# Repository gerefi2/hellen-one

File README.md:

# TL,DR: 

hellen-one is a toolset to produce custom PCBs by merging gerber files of known proven functional modules into trivial _frame_ PCB with mostly just the main vehicle connector.

* fork https://github.com/gerefi/hellen-example/ repo to get github actions and meta files
* make sure github actions are enabled/enable github actions on your fork
* replace xxx and yyy in ``revision.txt`` with name of your board
* create youboard.kicad_pcb from [proven modules](https://github.com/gerefi2/hellen-one/tree/master/modules) using KiCAD 6 or 7
* push into github to trigger hellen-one gerber expert and gerber merge (that's where the hellen magic happens! for instance gerber export is taken care by [export.sh](https://github.com/gerefi2/hellen-one/blob/master/kicad/bin/export.sh) script which github action would invoke _automatically_. Just watch for the yellow circle to turn into a green checkmark.)
* (sorry rotation only by factor of 90 degrees at this point)
* order your using fabrication files from 'boards' folder!

Please see how some of the open source boards are done and follow the pattern:

## Open Source Boards

* https://github.com/gerefi/alphax-4chan
* https://github.com/gerefi/uaefi
* https://github.com/gerefi/alphax-2chan
* https://github.com/gerefi/hellen154hyundai
* https://github.com/gerefi/hellen121vag
* https://github.com/gerefi/hellen88bmw
* https://github.com/gerefi2/hellen81/

This repository contains all scripts and data to create Hellen One boards for [gerefi](https://github.com/gerefi/gerefi)!

See also https://github.com/gerefi/gerefi/wiki/Hellen-One-Platform

Hellen One is a DIY PnP ECU board construction toolset.

Do you have a car with a rare or non-standard ECU connector pinout?
Do you want a custom DIY ECU but don't want to design it from scratch?

Then Hellen One is for you!

Please see Hellen One Wiki for more info:

https://github.com/gerefi2/hellen-one/wiki

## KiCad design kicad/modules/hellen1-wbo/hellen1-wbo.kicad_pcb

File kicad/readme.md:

# Some of the modules were designed in KiCAD

If you are designing a new ECU frame see https://github.com/gerefi2/hellen-one/tree/master/modules

doThis folder contains module _source_ files, not reusable resulting frames like [here](../modules).

See https://github.com/gerefi2/hellen-one/wiki/scripts-howto#how-to-create-a-module

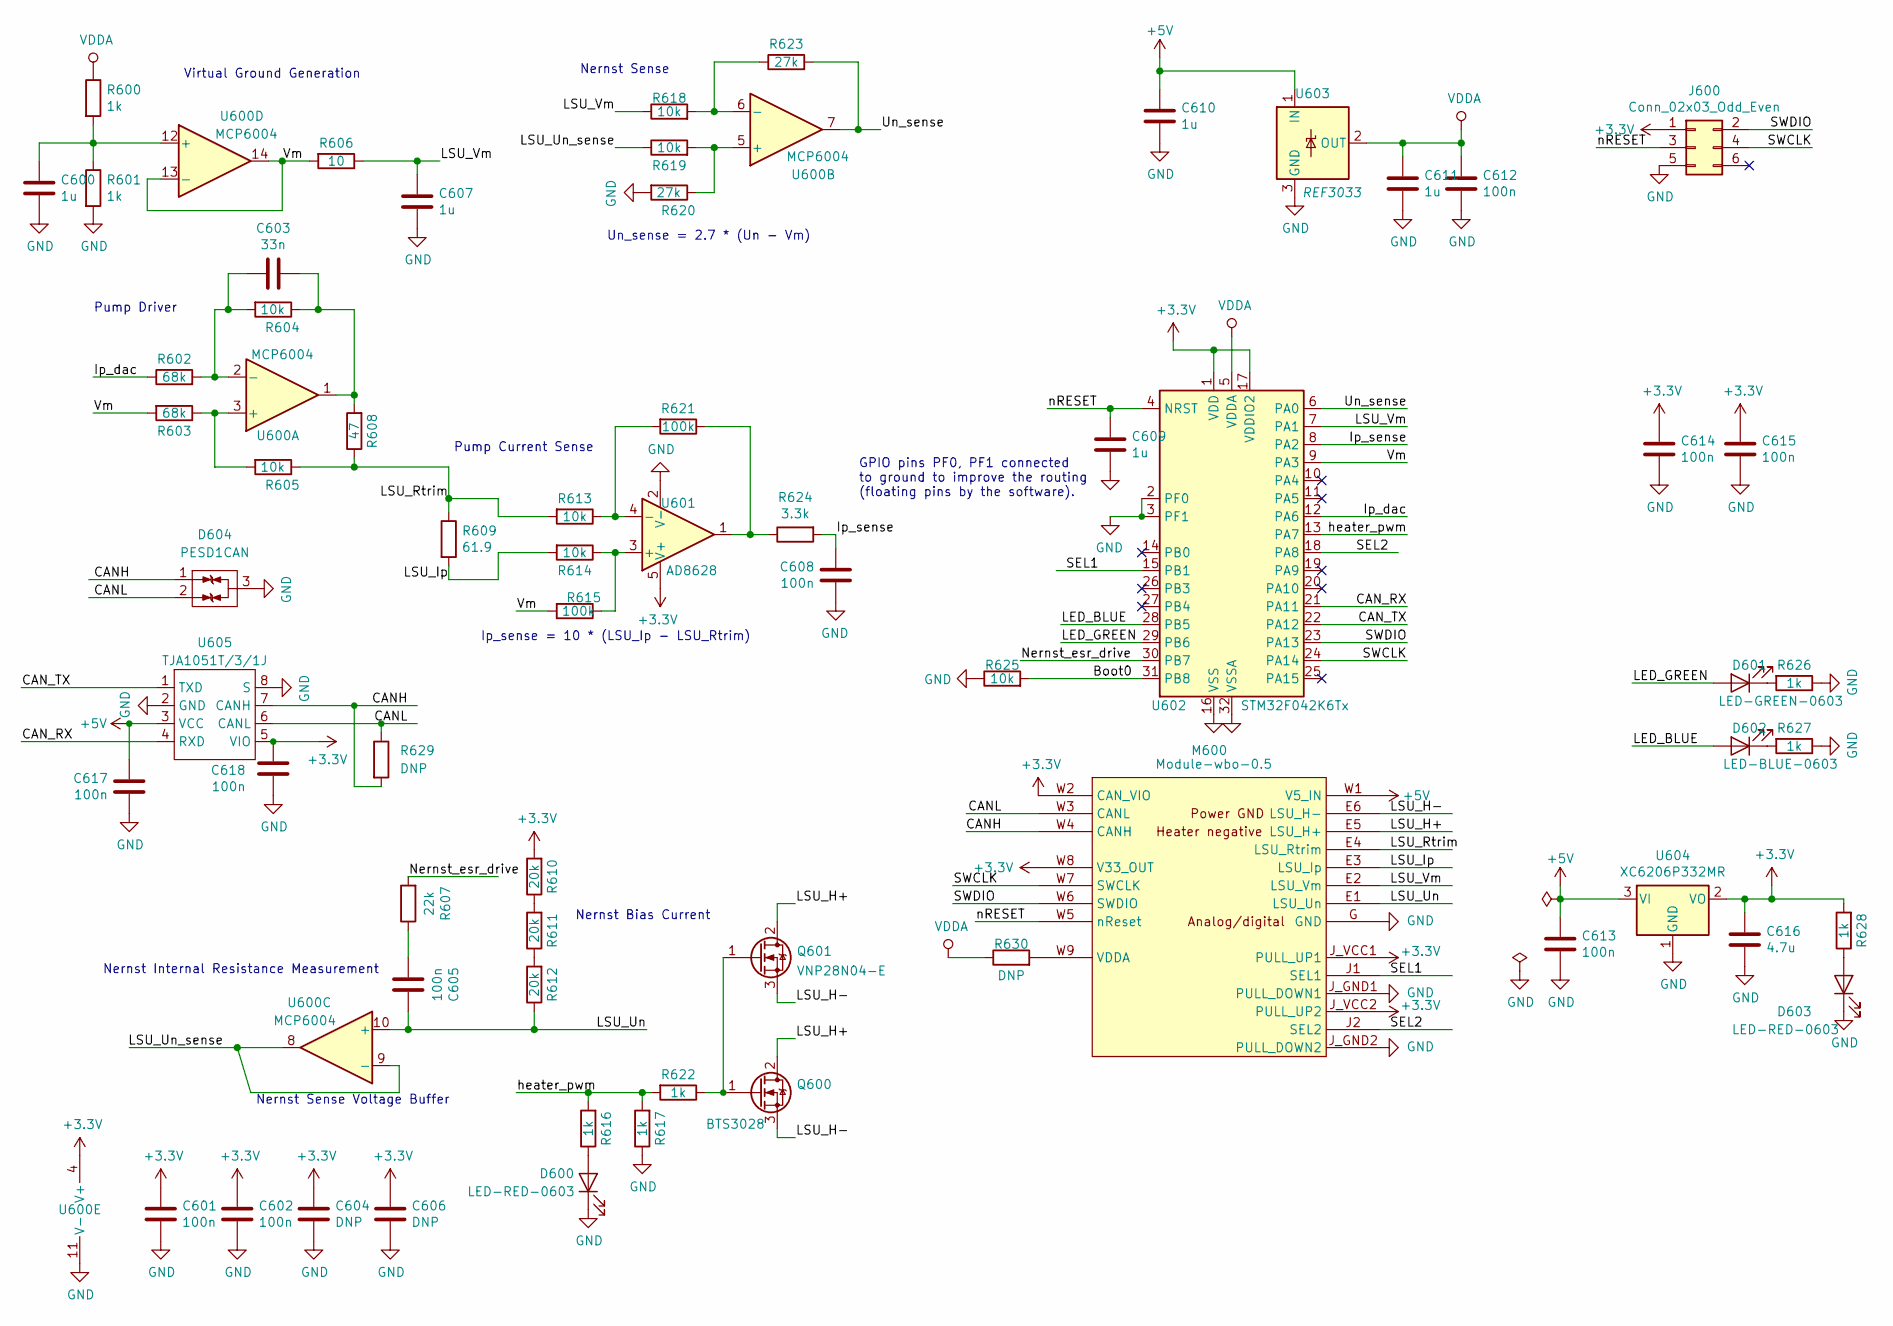
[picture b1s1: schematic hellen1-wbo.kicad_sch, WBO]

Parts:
C600, C607, C609, C610, C611: 1u; C_0402_1005Metric; LCSC C52923
C601, C602, C605, C608, C612, C613, C614, C615, C617, C618: 100n; C_0402_1005Metric; LCSC C1525
C603: 33n; C_0402_1005Metric; LCSC C1585
C604, C606: DNP; C_0402_1005Metric
C616: 4.7u; C_0603_1608Metric; LCSC C19666
D600, D603: LED-RED-0603; LED_0603_1608Metric; LCSC C2286
D601: LED-GREEN-0603; LED_0603_1608Metric; LCSC C72043
D602: LED-BLUE-0603; LED_0603_1608Metric; LCSC C72041
D604: PESD1CAN; SOT-23; LCSC C343993
J600: Conn_02x03_Odd_Even; Tag-Connect_TC2030-IDC-NL_2x03_P1.27mm_Vertical
M600: Module-wbo-0.5; wbo
Q600: BTS3028; TO-252-2; LCSC C112639
Q601: VNP28N04-E; TO-220-3_Vertical; LCSC C263002
R600, R601, R616, R617, R622, R626, R627, R628: 1k; R_0402_1005Metric; LCSC C11702
R602, R603: 68k; R_0402_1005Metric; LCSC C36871
R604, R605, R613, R614, R618, R619, R625: 10k; R_0402_1005Metric; LCSC C25744
R606: 10; R_0402_1005Metric; LCSC C25077
R607: 22k; R_0402_1005Metric; LCSC C25768
R608: 47; R_0402_1005Metric; LCSC C25118
R609: 61.9; R_0603_1608Metric; LCSC C23092
R610, R611, R612: 20k; R_0402_1005Metric; LCSC C25765
R615, R621: 100k; R_0402_1005Metric; LCSC C25741
R620, R623: 27k; R_0402_1005Metric; LCSC C25771
R624: 3.3k; R_0402_1005Metric; LCSC C25890
R629, R630: DNP; R_0402_1005Metric
U600: MCP6004; TSSOP-14_4.4x5mm_P0.65mm; LCSC C50282
U601: AD8628; TSOT-23-5; LCSC C29309
U602: STM32F042K6Tx; LQFP-32_7x7mm_P0.8mm; LCSC C69216
U603: REF3033; SOT-23; LCSC C36658
U604: XC6206P332MR; SOT-23; LCSC C5446
U605: TJA1051T/3/1J; SO-8_3.9x4.9mm_P1.27mm; LCSC C38695

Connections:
+3V3: C601.1, C602.1, C604.1, C606.1, C614.1, C615.1, C616.1, C618.1, J600.1, M600.J_VCC1 (PULL_UP1), M600.J_VCC2 (PULL_UP2), M600.W2 (CAN_VIO), M600.W8 (V33_OUT), R610.2, R628.2, U600.4 (V+), U601.5 (V+), U602.1 (VDD), U602.17 (VDDIO2), U604.2 (VO), U605.5 (VIO)
+5V: C610.1, C613.1, C617.1, M600.W1 (V5_IN), U603.1 (IN), U604.3 (VI), U605.3 (VCC)
/Boot0: R625.2, U602.31 (PB8)
/CANH: D604.1 (G), M600.W4 (CANH), R629.2, U605.7 (CANH)
/CANL: D604.2 (D), M600.W3 (CANL), R629.1, U605.6 (CANL)
/CAN_RX: U602.21 (PA11), U605.4 (RXD)
/CAN_TX: U602.22 (PA12), U605.1 (TXD)
/Ip_dac: R602.1, U602.12 (PA6)
/Ip_sense: C608.1, R624.2, U602.8 (PA2)
/LED_BLUE: D602.2 (A), U602.28 (PB5)
/LED_GREEN: D601.2 (A), U602.29 (PB6)
/LSU_H+: M600.E5 (LSU_H+), Q600.2 (D), Q601.2 (D)
/LSU_H-: M600.E6 (LSU_H-), Q600.3 (S), Q601.3 (S)
/LSU_Ip: M600.E3 (LSU_Ip), R609.2, R614.2
/LSU_Rtrim: M600.E4 (LSU_Rtrim), R605.1, R608.1, R609.1, R613.2
/LSU_Un: C605.1, M600.E1 (LSU_Un), R612.1, U600.10 (+)
/LSU_Un_sense: R619.1, U600.8, U600.9 (-)
/LSU_Vm: C607.1, M600.E2 (LSU_Vm), R606.1, R618.1, U602.7 (PA1)
/Nernst_esr_drive: R607.2, U602.30 (PB7)
/SEL1: M600.J1 (SEL1), U602.15 (PB1)
/SEL2: M600.J2 (SEL2), U602.18 (PA8)
/SWCLK: J600.4, M600.W7 (SWCLK), U602.24 (PA14)
/SWDIO: J600.2, M600.W6 (SWDIO), U602.23 (PA13)
/Un_sense: R623.2, U600.7, U602.6 (PA0)
/Vm: R603.2, R606.2, R615.2, U600.13 (-), U600.14, U602.9 (PA3)
/heater_pwm: R616.2, R617.2, R622.2, U602.13 (PA7)
/nRESET: C609.1, J600.3, M600.W5 (nReset), U602.4 (NRST)
GND: C600.2, C601.2, C602.2, C604.2, C606.2, C607.2, C608.2, C609.2, C610.2, C611.2, C612.2, C613.2, C614.2, C615.2, C616.2, C617.2, C618.2, D600.1 (K), D603.1 (K), D604.3 (S), J600.5, M600.G (GND), M600.J_GND1 (PULL_DOWN1), M600.J_GND2 (PULL_DOWN2), R601.2, R617.1, R620.2, R625.1, R626.1, R627.1, U600.11 (V-), U601.2 (V-), U602.2 (PF0), U602.3 (PF1), U602.16 (VSS), U602.32 (VSSA), U603.3 (GND), U604.1 (GND), U605.2 (GND), U605.8 (S)
unnamed: C600.1, R600.2, R601.1, U600.12 (+)
unnamed: C603.1, R604.1, R608.2, U600.1
unnamed: C603.2, R602.2, R604.2, U600.2 (-)
unnamed: C605.2, R607.1
unnamed: D600.2 (A), R616.1
unnamed: D601.1 (K), R626.2
unnamed: D602.1 (K), R627.2
unnamed: D603.2 (A), R628.1
unnamed: M600.W9 (VDDA), R630.2
unnamed: Q600.1 (G), Q601.1 (G), R622.1
unnamed: R603.1, R605.2, U600.3 (+)
unnamed: R610.1, R611.2
unnamed: R611.1, R612.2
unnamed: R613.1, R621.2, U601.4 (-)
unnamed: R614.1, R615.1, U601.3 (+)
unnamed: R618.2, R623.1, U600.6 (-)
unnamed: R619.2, R620.1, U600.5 (+)
unnamed: R621.1, R624.1, U601.1
VDDA: C611.1, C612.1, R600.1, R630.1, U602.5 (VDDA), U603.2 (OUT)

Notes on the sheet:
Nernst Sense
Pump Driver
Virtual Ground Generation
Nernst Internal Resistance Measurement
Nernst Bias Current
Nernst Sense Voltage Buffer
Un_sense = 2.7 * (Un - Vm)
Pump Current Sense
Ip_sense = 10 * (LSU_Ip - LSU_Rtrim)
GPIO pins PF0, PF1 connected to ground to improve the routing (floating pins by the software).

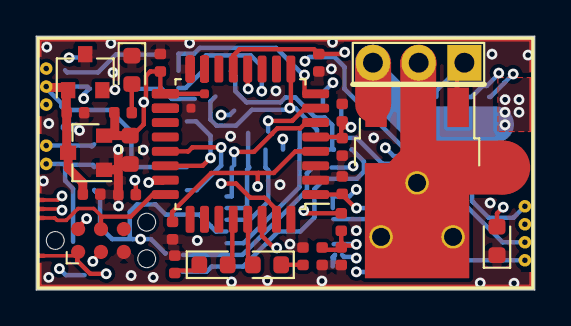
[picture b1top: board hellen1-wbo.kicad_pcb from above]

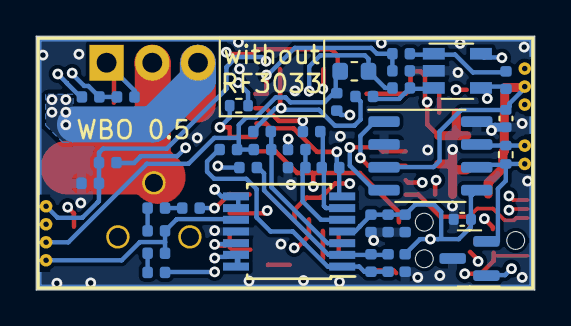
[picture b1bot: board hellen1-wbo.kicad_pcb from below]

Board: 4 copper layers, 27.7 x 14.1 mm, 65 parts (38 on the bottom side), 47 nets.

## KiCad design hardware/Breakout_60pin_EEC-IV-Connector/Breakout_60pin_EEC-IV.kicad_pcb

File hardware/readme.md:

# Connectors
Some vehicle-specific connector boards are also pretty nice if you want to keep original harness intact

See [Connectors wiki page](http://gerefi.com/wiki/index.php?title=Hardware:OEM_connectors)
todo: move Connectors wiki page content into git

* [35 pin](Breakout_35pin_MX7-C-35PL-C11-connector) Mazda TCU
* [38 pin](Breakout_38pin_NGC-connector) Chrysler NGC connector
* [48 pin](Breakout_48pin_174917-Connector) Mazda Miata NA6
* [52 pin](Breakout_52pin_172319-1-Connector) Mitsubishi Galant VR4
* [55 pin](Breakout_55pin_963063-15-Connector) TE Lada
* [55 pin](breakout_55pin-motronic-Connector) Motronic 1.5.x BMW/GM
* [60 pin](Breakout_60pin_EEC-IV-Connector) Ford EEC-IV
* [64 pin](Breakout_64pin_176122-6-Connector) Mazda Miata NA NB1, Honda Civic
* [68 pin](Breakout_68pin_966595-1_and_963356-1-Connector) Volkswagen Audi VAG
* [72 pin](Breakout_72pin_1123038-2-Connector) Mazda Miata NB2
* [88 pin](Breakout_88pin_VAG-Connector) Volkswagen Audi VAG
* [121 pin](Breakout_121pin_368255-2-Connector) Volkswagen Audi VAG
* [134 pin](Breakout_134pin_7-967288-1-Connector) BWM
* [154 pin](Breakout_154pin_284617-1-Connector) Volkswagen Audi VAG

# Modules
* [stm32 Brain board 48pin](mini48-stm32)
* [stm32 Brain board 100pin](brain_board)
* [stm32 Brain board 176pin](brain_board_176-pin)
* [CAN module](can_board) CAN using SN65HVD230
* [VR module](VR_Board) Variable Reluctance conditioner board VR MAX9926
* [Wideband module](CJ125_board) CJ125 Bosch Wideband board
* [VND5E025AKTR](PowerSSO-24_breakout) double channel high-side driver with analog current sense (used on Dodge Neon 2003 test mule)
* [BTS21400](DDPAK_breakout) ignition coil IGBT driver (used on Dodge Neon 2003 test mule)
* [TLE6240 module](low_side_tle6240) integrated low side switch (fabricated, not tested)
* [TLE6244 module](Breakout_TLE6244) integrated low side switch (never actually fabricated)
* [TLE8810ED module](https://github.com/gerefi/hw_modular/tree/master/TLE8110ED_breakout_board) integrated low side switch
* [MC33816](Common_Rail_MC33816) common rail driver - gerefi has working GDI*
* [LM1949]([Low-Z_LM1949](https://github.com/gerefi/hw_legacy/tree/master/Low-Z_LM1949)) low impedance injector driver (never actually fabricated)

New modules are being added to https://github.com/gerefi/hw_modular

Some stuff we have given up on completely is located at https://github.com/gerefi/hw_legacy

Above mentioned modules are known to work unless stated otherwise

### More gerefi hardware

See https://github.com/gerefi/gerefi/wiki/Hardware

# Frankenso
Frankenso has moved to https://github.com/gerefi/gerefi-hardware/tree/main/classic-designs

# More info

 [Interactive Html Boms](https://gerefi.com/docs/ibom/)

See [Hardware status forum thread](http://gerefi.com/forum/viewtopic.php?f=4&t=260)
todo: move hardware status content into git

# Important note
gerefi is currently transitioning from KiCAD 4 to KiCAD 5.

# Important note

Depends on libraries from https://github.com/gerefi/kicad-libraries

If you download complete repo do not forget to download libraries. If you git clone be sure to also

`git submodule update --init`

`git submodule update --init`

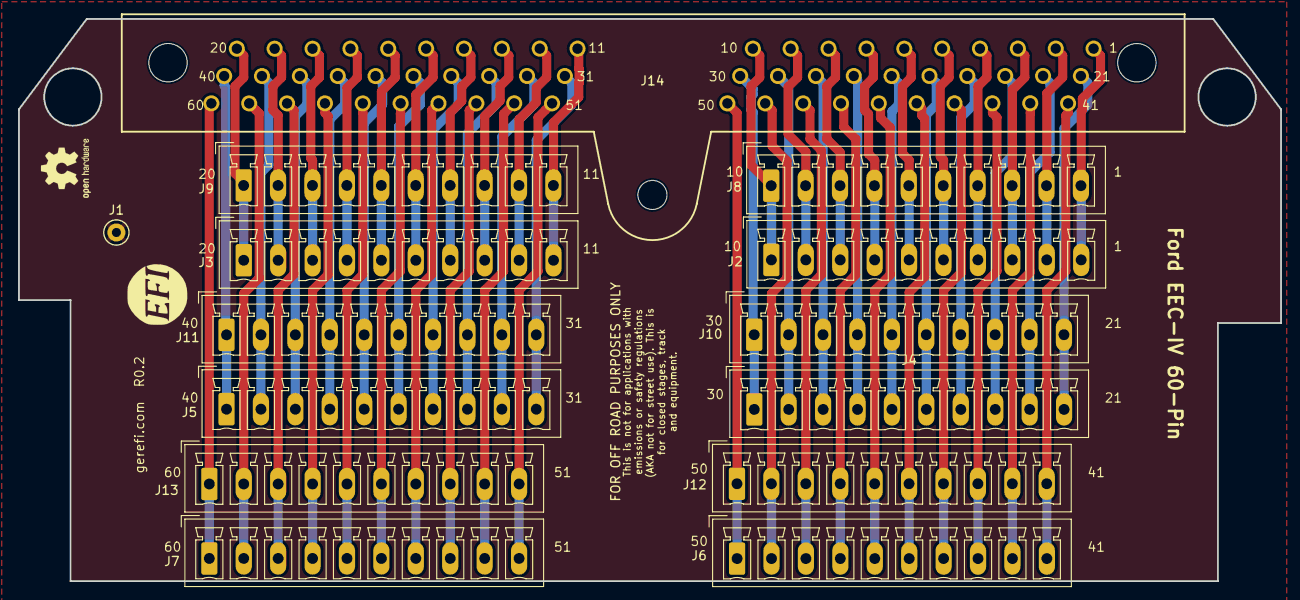
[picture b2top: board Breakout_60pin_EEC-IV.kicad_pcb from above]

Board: 2 copper layers, 139.7 x 62.2 mm, 17 parts (0 on the bottom side), 60 nets.

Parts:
G1: Disclaimer; Off_Road_Disclaimer
G2: LOGO
J1: Conn_01x01; TestPoint_Keystone_5000-5004_Miniature
J2, J3, J4, J5, J6, J7, J8, J9, J10, J11, J12, J13: Conn_01x10; PhoenixContact_MCV_1,5_10-G-3.81_1x10_P3.81mm_Vertical
J14: EEC-IV; eeciv
LOGO1: DNP; OSHW-Logo2_7.3x6mm_SilkScreen

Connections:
/1: J2.10, J8.10, J14.1
/5: J2.6, J8.6, J14.5
/10: J2.1, J8.1, J14.10
/11: J3.10, J9.10, J14.11
/15: J3.6, J9.6, J14.15
/25: J4.6, J10.6, J14.25
/30: J4.1, J10.1, J14.30
/31: J5.10, J11.10, J14.31
/35: J5.6, J11.6, J14.35
/40: J5.1, J11.1, J14.40
/41: J6.10, J12.10, J14.41
/45: J6.6, J12.6, J14.45
/50: J6.1, J12.1, J14.50
/53: J7.8, J13.8, J14.53
/54: J7.7, J13.7, J14.54
/55: J7.6, J13.6, J14.55
/60: J7.1, J13.1, J14.60
/420: J3.1, J9.1, J14.20
/421: J4.10, J10.10, J14.21
unnamed: J4.2, J10.2, J14.29
unnamed: J4.3, J10.3, J14.28
unnamed: J4.4, J10.4, J14.27
unnamed: J4.5, J10.5, J14.26
unnamed: J4.7, J10.7, J14.24
unnamed: J4.8, J10.8, J14.23
unnamed: J4.9, J10.9, J14.22
unnamed: J5.2, J11.2, J14.39
unnamed: J5.3, J11.3, J14.38
unnamed: J5.4, J11.4, J14.37
unnamed: J5.5, J11.5, J14.36
unnamed: J5.7, J11.7, J14.34
unnamed: J5.8, J11.8, J14.33
unnamed: J5.9, J11.9, J14.32
unnamed: J6.2, J12.2, J14.49
unnamed: J6.3, J12.3, J14.48
unnamed: J6.4, J12.4, J14.47
unnamed: J6.5, J12.5, J14.46
unnamed: J6.7, J12.7, J14.44
unnamed: J6.8, J12.8, J14.43
unnamed: J6.9, J12.9, J14.42
unnamed: J7.2, J13.2, J14.59
unnamed: J7.3, J13.3, J14.58
unnamed: J7.4, J13.4, J14.57
unnamed: J7.5, J13.5, J14.56
unnamed: J7.9, J13.9, J14.52
unnamed: J7.10, J13.10, J14.51
unnamed: J2.9, J8.9, J14.2
unnamed: J2.8, J8.8, J14.3
unnamed: J2.7, J8.7, J14.4
unnamed: J2.5, J8.5, J14.6
unnamed: J2.4, J8.4, J14.7
unnamed: J2.3, J8.3, J14.8
unnamed: J2.2, J8.2, J14.9
unnamed: J3.9, J9.9, J14.12
unnamed: J3.8, J9.8, J14.13
unnamed: J3.7, J9.7, J14.14
unnamed: J3.5, J9.5, J14.16
unnamed: J3.4, J9.4, J14.17
unnamed: J3.3, J9.3, J14.18
unnamed: J3.2, J9.2, J14.19

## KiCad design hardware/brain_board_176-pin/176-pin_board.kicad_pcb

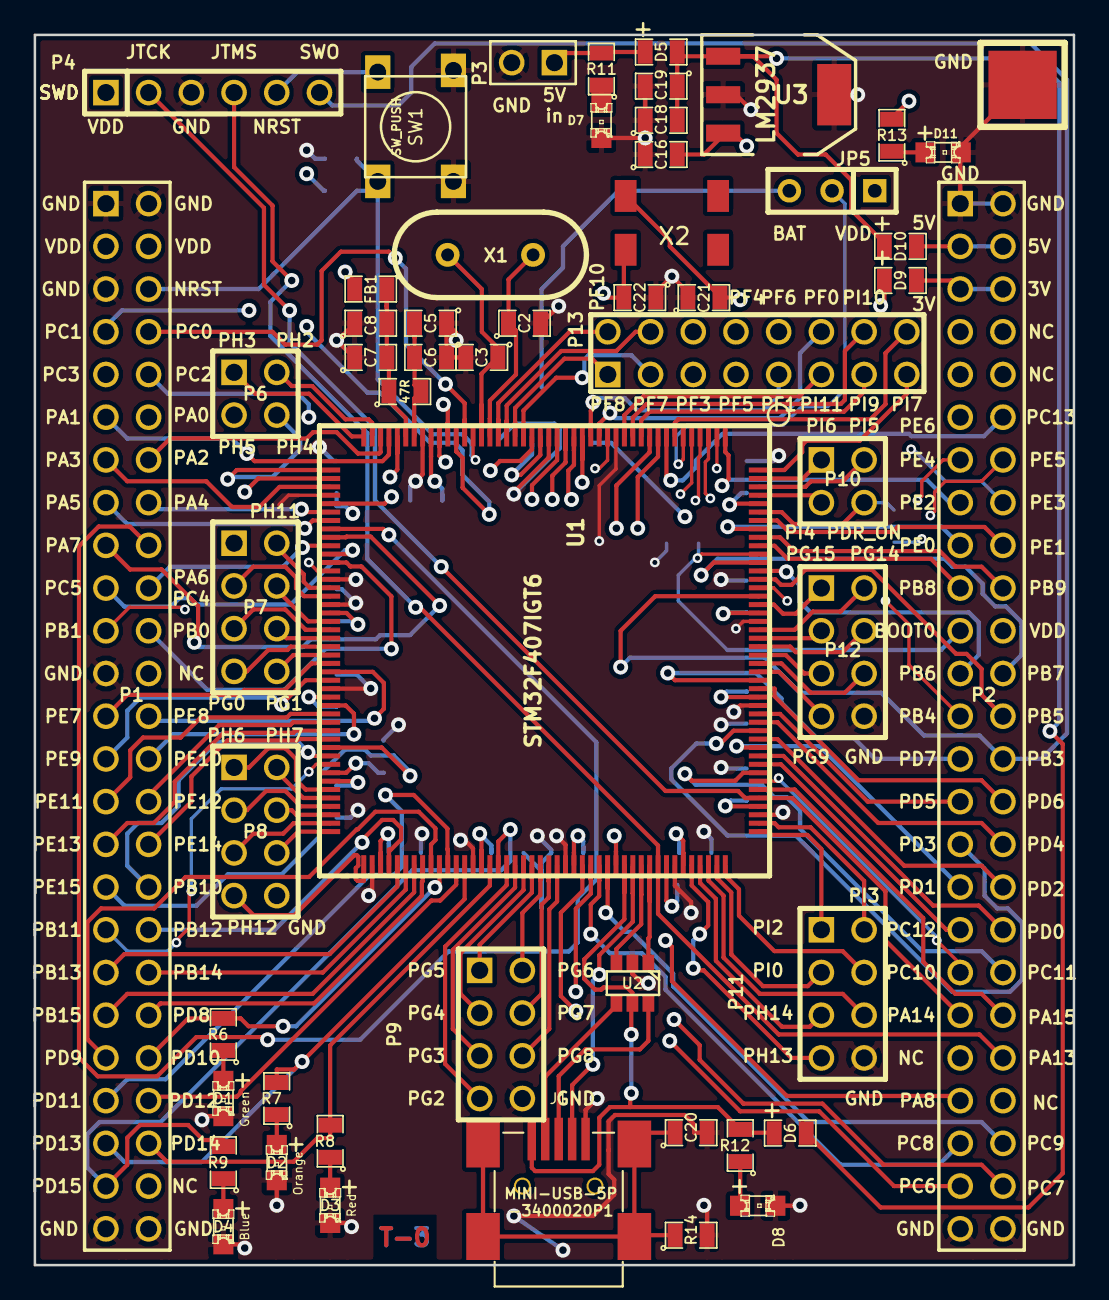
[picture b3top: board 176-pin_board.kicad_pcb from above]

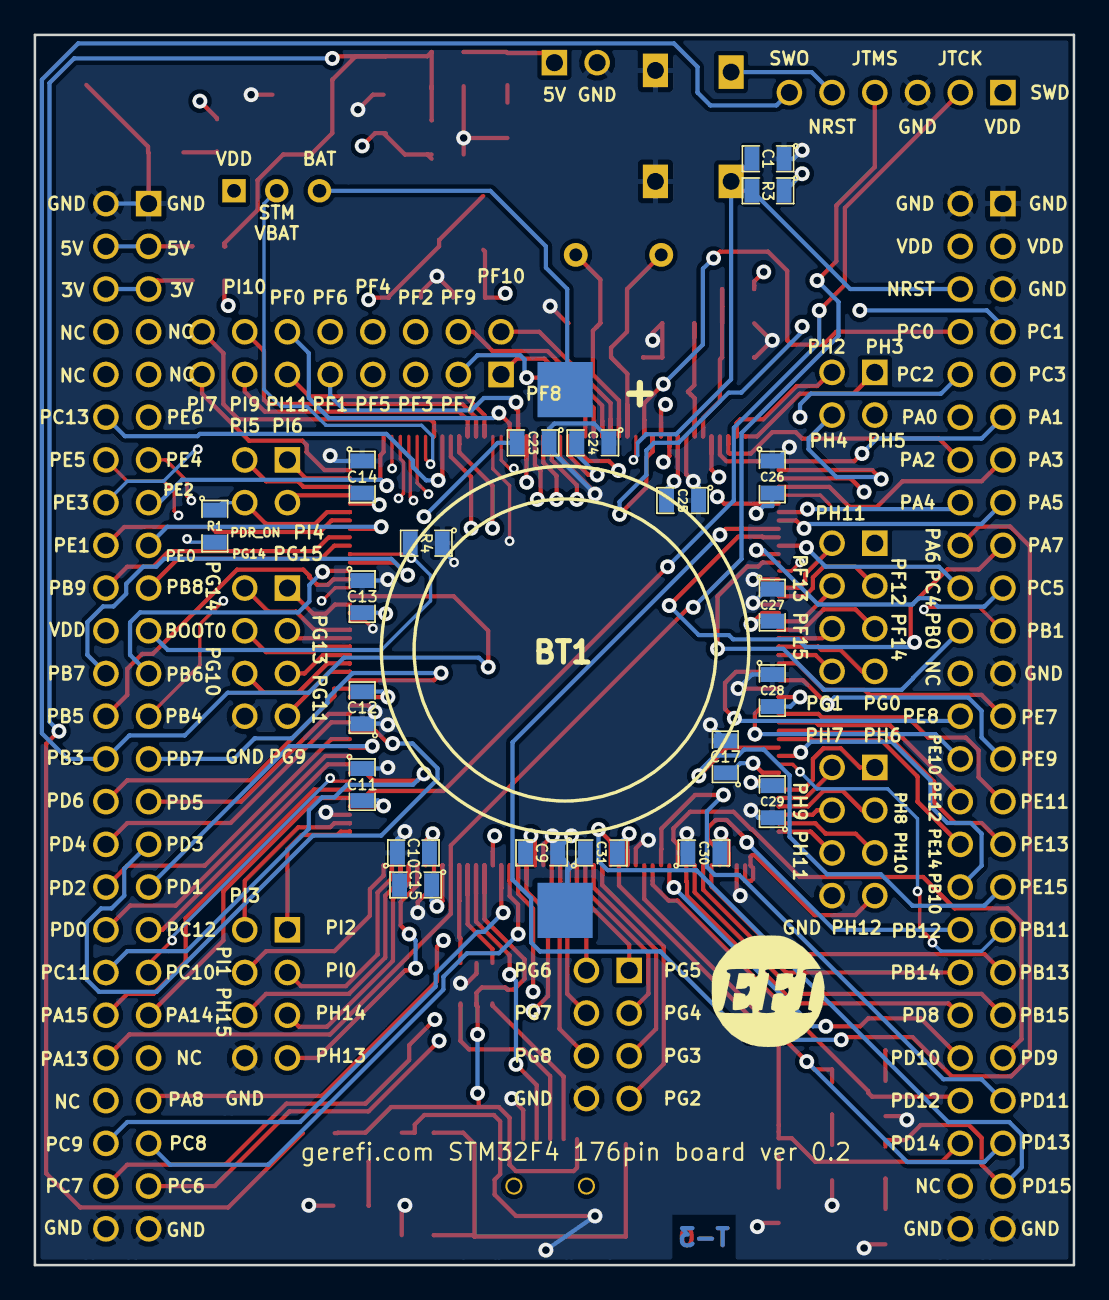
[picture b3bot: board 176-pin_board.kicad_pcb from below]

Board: 4 copper layers, 61.8 x 73.2 mm, 77 parts (23 on the bottom side), 164 nets.

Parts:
BT1: BATTERY_CR2032; BATT_CR2032_MPD
C1: 0.02uF; SM0805
C2, C3, C21, C22: 18pF; SM0805
C5, C8: 0.01uF; SM0805
C6, C7, C16: 1uF; SM0805
C9, C10, C11, C12, C13, C14, C18, C20, C23, C24, C25, C26, C27, C28, C29, C30, C31: 0.1uF; SM0805
C15, C17: 2u2F; SM0805
C19: 4.7uF; SM0805
D1, D2, D3, D4, D7, D8, D11: LED_0805; LED-0805_A
D5, D6, D9, D10: DIODESCH; SM0805-diode
FB1: FILTER; SM0805
G1: LOGO; LOGO_F
J1: MINI-USB-5P-3400020P1
JP5: JUMPER3; SIL-3
P1, P2: CONN_25X2; PIN_ARRAY_25x2_A
P3: CONN_2; PIN_ARRAY_2_A
P4: CONN_6; PIN_ARRAY-6X1
P5: CONN_1; 1PIN_SMD
P6, P10: CONN_2X2; PIN_ARRAY_2X2
P7, P8, P9, P11, P12: CONN_4X2; pin_array_4x2
P13: CONN_8X2; pin_array_8x2
R1, R11, R12, R13: 1k; SM0805
R3, R4: 10k; SM0805
R6, R7, R8, R9: 680R; SM0805
R10: 47R; SM0805
R14: 100k; SM0805
SW1: SW_PUSH; TL-1105
U1: STM32F407IGT6; LQFP-176
U2: NUF2101MT1G; SOT-457
U3: LM2937; SOT223
X1: CRYSTAL; HC-49V
X2: CRYSTAL(MC306); MC-306

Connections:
/3.3V: D9.2, P2.5, P2.6
/5V: D10.2, P2.3, P2.4
/5Vi: C18.2, C19.1, D5.2, D6.2, D10.1, U3.1
/BOOT0: P2.21, R4.2, U1.166
/D+: J1.3, U2.6
/D-: J1.2, U2.4
/NRST: C1.2, P1.6, P4.5, R3.2, SW1.1, U1.31
/PA0: P1.12, U1.40
/PA1: P1.11, U1.41
/PA2: P1.14, U1.42
/PA3: P1.13, U1.47
/PA4: P1.16, U1.50
/PA5: P1.15, U1.51
/PA6: P1.18, U1.52
/PA7: P1.17, U1.53
/PA8: P2.43, U1.119
/PA9: D6.1, J1.1, R12.2, U1.120, U2.5
/PA10: J1.4, U1.121
/PA11: U1.122, U2.3
/PA12: U1.123, U2.1
/PA13: P2.42, P4.4, U1.124
/PA14: P2.39, P4.2, U1.137
/PA15: P2.40, U1.138
/PB0: P1.22, U1.56
/PB1: P1.21, U1.57
/PB3: P2.28, P4.6, U1.161
/PB4: P2.25, U1.162
/PB5: P2.26, U1.163
/PB6: P2.23, U1.164
/PB7: P2.24, U1.165
/PB8: P2.19, U1.167
/PB9: P2.20, U1.168
/PB10: P1.34, U1.79
/PB11: P1.35, U1.80
/PB12: P1.36, U1.92
/PB13: P1.37, U1.93
/PB14: P1.38, U1.94
/PB15: P1.39, U1.95
/PC0: P1.8, U1.32
/PC1: P1.7, U1.33
/PC2: P1.10, U1.34
/PC3: P1.9, U1.35
/PC4: P1.20, U1.54
/PC5: P1.19, U1.55
/PC6: P2.47, U1.115
/PC7: P2.48, U1.116
/PC8: P2.45, U1.117
/PC9: P2.46, U1.118
/PC10: P2.37, U1.139
/PC11: P2.38, U1.140
/PC12: P2.35, U1.141
/PC13: P2.12, U1.8
/PD0: P2.36, U1.142
/PD1: P2.33, U1.143
/PD2: P2.34, U1.144
/PD3: P2.31, U1.145
/PD4: P2.32, U1.146
/PD5: P2.29, U1.147
/PD6: P2.30, U1.150
/PD7: P2.27, U1.151
/PD8: P1.40, U1.96
/PD9: P1.41, U1.97
/PD10: P1.42, R6.2, U1.98
/PD11: P1.43, U1.99
/PD12: P1.44, U1.100
/PD13: P1.45, R7.2, U1.101
/PD14: P1.46, R8.2, U1.104
/PD15: P1.47, R9.2, U1.105
/PDR_ON: P10.4, R1.1, U1.171
/PE0: P2.17, U1.169
/PE1: P2.18, U1.170
/PE2: P2.15, U1.1
/PE3: P2.16, U1.2
/PE4: P2.13, U1.3
/PE5: P2.14, U1.4
/PE6: P2.11, U1.5
/PE7: P1.25, U1.68
/PE8: P1.26, U1.69
/PE9: P1.27, U1.70
/PE10: P1.28, U1.73
/PE11: P1.29, U1.74
/PE12: P1.30, U1.75
/PE13: P1.31, U1.76
/PE14: P1.32, U1.77
/PE15: P1.33, U1.78
/PF0: P13.12, U1.16
/PF1: P13.9, U1.17
/PF2: P13.6, U1.18
/PF3: P13.5, U1.19
/PF4: P13.8, U1.20
/PF5: P13.7, U1.21
/PF6: P13.10, U1.24
/PF7: P13.3, U1.25
/PF8: P13.1, U1.26
/PF9: P13.4, U1.27
/PF10: P13.2, U1.28
/PF11: P7.2, U1.59
/PF12: P7.3, U1.60
/PF13: P7.4, U1.63
/PF14: P7.5, U1.64
/PF15: P7.6, U1.65
/PG0: P7.7, U1.66
/PG1: P7.8, U1.67
/PG2: P9.7, U1.106
/PG3: P9.5, U1.107
/PG4: P9.3, U1.108
/PG5: P9.1, U1.109
/PG6: P9.2, U1.110
/PG7: P9.4, U1.111
/PG8: P9.6, U1.112
/PG9: P12.7, U1.152
/PG10: P12.6, U1.153
/PG11: P12.5, U1.154
/PG12: P12.4, U1.155
/PG13: P12.3, U1.156
/PG14: P12.2, U1.157
/PG15: P12.1, U1.160
/PH0: C2.1, U1.29, X1.2
/PH1: C3.1, U1.30, X1.1
/PH2: P6.2, U1.43
/PH3: P6.1, U1.44
/PH4: P6.4, U1.45
/PH5: P6.3, U1.46
/PH6: P8.1, U1.83
/PH7: P8.2, U1.84
/PH8: P8.3, U1.85
/PH9: P8.4, U1.86
/PH10: P8.5, U1.87
/PH11: P8.6, U1.88
/PH12: P8.7, U1.89
/PH13: P11.7, U1.128
/PH14: P11.5, U1.129
/PH15: P11.6, U1.130
/PI0: P11.3, U1.131
/PI1: P11.4, U1.132
/PI2: P11.1, U1.133
/PI3: P11.2, U1.134
/PI4: P10.3, U1.173
/PI5: P10.2, U1.174
/PI6: P10.1, U1.175
/PI7: P13.15, U1.176
/PI8: P13.16, U1.7
/PI9: P13.13, U1.11
/PI10: P13.14, U1.12
/PI11: P13.11, U1.13
/VBAT: JP5.2, U1.6
/VDD: C9.2, C10.2, C11.2, C12.2, C13.2, C14.2, C16.2, C23.2, C24.2, C25.2, C26.2, C27.2, C28.2, C29.2, C30.2, C31.2, D9.1, FB1.2, JP5.1, P1.3, P1.4, P2.22, P4.1, R1.2, R3.1, R13.2, U1.15, U1.23, U1.36, U1.49, U1.62, U1.72, U1.82, U1.91, U1.103, U1.114, U1.127, U1.136, U1.149, U1.159, U1.172, U3.3
GND: BT1.2, C1.1, C2.2, C3.2, C5.1, C6.1, C7.1, C8.1, C9.1, C10.1, C11.1, C12.1, C13.1, C14.1, C15.2, C16.1, C17.2, C18.1, C19.2, C20.2, C21.1, C22.1, C23.1, C24.1, C25.1, C26.1, C27.1, C28.1, C29.1, C30.1, C31.1, D1.2, D2.2, D3.2, D4.2, D7.2, D8.2, D11.2, J1.5, P1.1, P1.2, P1.5, P1.23, P1.49, P1.50, P2.1, P2.2, P2.49, P2.50, P3.2, P4.3, P5.1, P8.8, P9.8, P11.8, P12.8, R4.1, R14.2, SW1.2, U1.14, U1.22, U1.37, U1.48, U1.58, U1.61, U1.71, U1.90, U1.102, U1.113, U1.126, U1.135, U1.148, U1.158, U2.2, U3.2, U3.4
unnamed: C7.2, C8.2, FB1.1, R10.1, U1.39
unnamed: D11.1, R13.1
unnamed: D2.1, R7.1
unnamed: D1.1, R6.1
unnamed: C5.2, C6.2, R10.2, U1.38
unnamed: D3.1, R8.1
unnamed: D5.1, P3.1, R11.2
unnamed: BT1.1, JP5.3
unnamed: D4.1, R9.1
unnamed: D7.1, R11.1
unnamed: D8.1, R12.1
unnamed: C20.1, J1.6, R14.1
unnamed: C21.2, U1.9, X2.4
unnamed: C22.2, U1.10, X2.1
unnamed: C15.1, U1.125
unnamed: C17.1, U1.81

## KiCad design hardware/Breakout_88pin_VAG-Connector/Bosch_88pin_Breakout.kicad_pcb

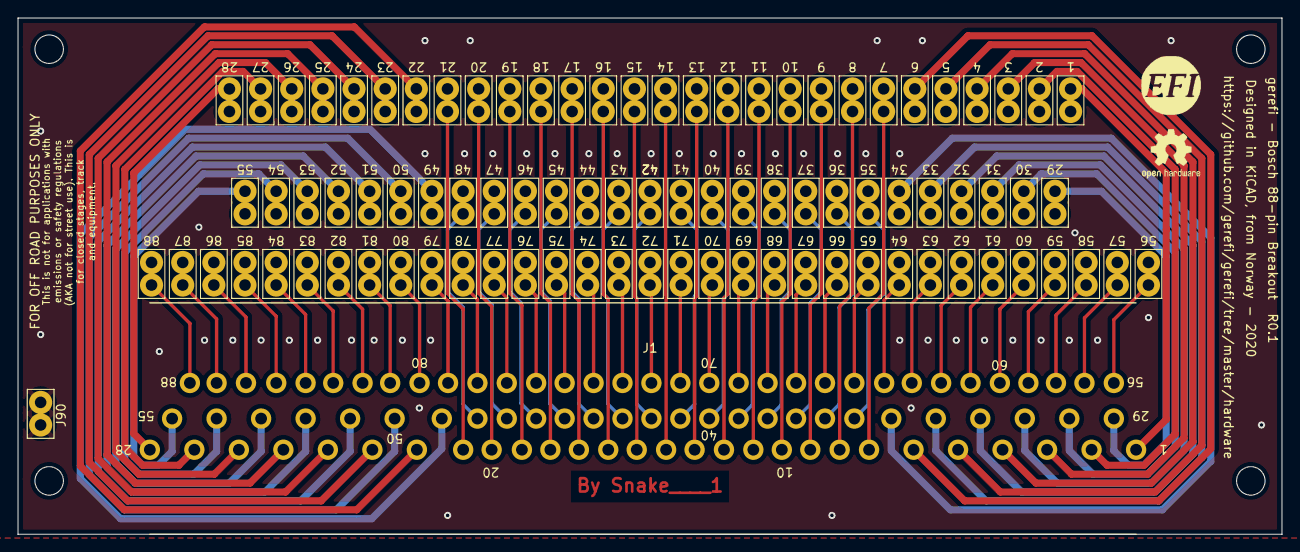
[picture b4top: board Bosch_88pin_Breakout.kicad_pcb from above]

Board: 2 copper layers, 142.0 x 58.0 mm, 97 parts (0 on the bottom side), 88 nets.

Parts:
G1: LOGO
G2: Disclaimer; Off_Road_Disclaimer
H1, H2, H3, H4: M3; MountingHole_3.2mm_M3_DIN965
J1: BOSCH_88PIN_02X44; BOSCH-88pin
J2: Pin1; TestPoint_Bridge_Pitch2.54mm_Drill1.3mm
J3: Pin3; TestPoint_Bridge_Pitch2.54mm_Drill1.3mm
J4: Pin5; TestPoint_Bridge_Pitch2.54mm_Drill1.3mm
J5: Pin7; TestPoint_Bridge_Pitch2.54mm_Drill1.3mm
J6: Pin9; TestPoint_Bridge_Pitch2.54mm_Drill1.3mm
J7: Pin11; TestPoint_Bridge_Pitch2.54mm_Drill1.3mm
J8: Pin13; TestPoint_Bridge_Pitch2.54mm_Drill1.3mm
J9: Pin15; TestPoint_Bridge_Pitch2.54mm_Drill1.3mm
J10: Pin17; TestPoint_Bridge_Pitch2.54mm_Drill1.3mm
J11: Pin19; TestPoint_Bridge_Pitch2.54mm_Drill1.3mm
J12: Pin21; TestPoint_Bridge_Pitch2.54mm_Drill1.3mm
J13: Pin23; TestPoint_Bridge_Pitch2.54mm_Drill1.3mm
J14: Pin25; TestPoint_Bridge_Pitch2.54mm_Drill1.3mm
J15: Pin27; TestPoint_Bridge_Pitch2.54mm_Drill1.3mm
J16: Pin29; TestPoint_Bridge_Pitch2.54mm_Drill1.3mm
J17: Pin31; TestPoint_Bridge_Pitch2.54mm_Drill1.3mm
J18: Pin33; TestPoint_Bridge_Pitch2.54mm_Drill1.3mm
J19: Pin35; TestPoint_Bridge_Pitch2.54mm_Drill1.3mm
J20: Pin37; TestPoint_Bridge_Pitch2.54mm_Drill1.3mm
J21: Pin39; TestPoint_Bridge_Pitch2.54mm_Drill1.3mm
J22: Pin41; TestPoint_Bridge_Pitch2.54mm_Drill1.3mm
J23: Pin43; TestPoint_Bridge_Pitch2.54mm_Drill1.3mm
J24: Pin45; TestPoint_Bridge_Pitch2.54mm_Drill1.3mm
J25: Pin47; TestPoint_Bridge_Pitch2.54mm_Drill1.3mm
J26: Pin49; TestPoint_Bridge_Pitch2.54mm_Drill1.3mm
J27: Pin51; TestPoint_Bridge_Pitch2.54mm_Drill1.3mm
J28: Pin53; TestPoint_Bridge_Pitch2.54mm_Drill1.3mm
J29: Pin55; TestPoint_Bridge_Pitch2.54mm_Drill1.3mm
J30: Pin57; TestPoint_Bridge_Pitch2.54mm_Drill1.3mm
J31: Pin59; TestPoint_Bridge_Pitch2.54mm_Drill1.3mm
J32: Pin61; TestPoint_Bridge_Pitch2.54mm_Drill1.3mm
J33: Pin63; TestPoint_Bridge_Pitch2.54mm_Drill1.3mm
J34: Pin65; TestPoint_Bridge_Pitch2.54mm_Drill1.3mm
J35: Pin67; TestPoint_Bridge_Pitch2.54mm_Drill1.3mm
J36: Pin69; TestPoint_Bridge_Pitch2.54mm_Drill1.3mm
J37: Pin71; TestPoint_Bridge_Pitch2.54mm_Drill1.3mm
J38: Pin73; TestPoint_Bridge_Pitch2.54mm_Drill1.3mm
J39: Pin75; TestPoint_Bridge_Pitch2.54mm_Drill1.3mm
J40: Pin77; TestPoint_Bridge_Pitch2.54mm_Drill1.3mm
J41: Pin79; TestPoint_Bridge_Pitch2.54mm_Drill1.3mm
J42: Pin81; TestPoint_Bridge_Pitch2.54mm_Drill1.3mm
J43: Pin83; TestPoint_Bridge_Pitch2.54mm_Drill1.3mm
J44: Pin85; TestPoint_Bridge_Pitch2.54mm_Drill1.3mm
J45: Pin87; TestPoint_Bridge_Pitch2.54mm_Drill1.3mm
J46: Pin2; TestPoint_Bridge_Pitch2.54mm_Drill1.3mm
J47: Pin4; TestPoint_Bridge_Pitch2.54mm_Drill1.3mm
J48: Pin6; TestPoint_Bridge_Pitch2.54mm_Drill1.3mm
J49: Pin8; TestPoint_Bridge_Pitch2.54mm_Drill1.3mm
J50: Pin10; TestPoint_Bridge_Pitch2.54mm_Drill1.3mm
J51: Pin12; TestPoint_Bridge_Pitch2.54mm_Drill1.3mm
J52: Pin14; TestPoint_Bridge_Pitch2.54mm_Drill1.3mm
J53: Pin16; TestPoint_Bridge_Pitch2.54mm_Drill1.3mm
J54: Pin18; TestPoint_Bridge_Pitch2.54mm_Drill1.3mm
J55: Pin20; TestPoint_Bridge_Pitch2.54mm_Drill1.3mm
J56: Pin22; TestPoint_Bridge_Pitch2.54mm_Drill1.3mm
J57: Pin24; TestPoint_Bridge_Pitch2.54mm_Drill1.3mm
J58: Pin26; TestPoint_Bridge_Pitch2.54mm_Drill1.3mm
J59: Pin28; TestPoint_Bridge_Pitch2.54mm_Drill1.3mm
J60: Pin30; TestPoint_Bridge_Pitch2.54mm_Drill1.3mm
J61: Pin32; TestPoint_Bridge_Pitch2.54mm_Drill1.3mm
J62: Pin34; TestPoint_Bridge_Pitch2.54mm_Drill1.3mm
J63: Pin36; TestPoint_Bridge_Pitch2.54mm_Drill1.3mm
J64: Pin38; TestPoint_Bridge_Pitch2.54mm_Drill1.3mm
J65: Pin40; TestPoint_Bridge_Pitch2.54mm_Drill1.3mm
J66: Pin42; TestPoint_Bridge_Pitch2.54mm_Drill1.3mm
J67: Pin44; TestPoint_Bridge_Pitch2.54mm_Drill1.3mm
J68: Pin46; TestPoint_Bridge_Pitch2.54mm_Drill1.3mm
J69: Pin48; TestPoint_Bridge_Pitch2.54mm_Drill1.3mm
J70: Pin50; TestPoint_Bridge_Pitch2.54mm_Drill1.3mm
J71: Pin52; TestPoint_Bridge_Pitch2.54mm_Drill1.3mm
J72: Pin54; TestPoint_Bridge_Pitch2.54mm_Drill1.3mm
J73: Pin56; TestPoint_Bridge_Pitch2.54mm_Drill1.3mm
J74: Pin58; TestPoint_Bridge_Pitch2.54mm_Drill1.3mm
J75: Pin60; TestPoint_Bridge_Pitch2.54mm_Drill1.3mm
J76: Pin62; TestPoint_Bridge_Pitch2.54mm_Drill1.3mm
J77: Pin64; TestPoint_Bridge_Pitch2.54mm_Drill1.3mm
J78: Pin66; TestPoint_Bridge_Pitch2.54mm_Drill1.3mm
J79: Pin68; TestPoint_Bridge_Pitch2.54mm_Drill1.3mm
J80: Pin70; TestPoint_Bridge_Pitch2.54mm_Drill1.3mm
J81: Pin72; TestPoint_Bridge_Pitch2.54mm_Drill1.3mm
J82: Pin74; TestPoint_Bridge_Pitch2.54mm_Drill1.3mm
J83: Pin76; TestPoint_Bridge_Pitch2.54mm_Drill1.3mm
J84: Pin78; TestPoint_Bridge_Pitch2.54mm_Drill1.3mm
J85: Pin80; TestPoint_Bridge_Pitch2.54mm_Drill1.3mm
J86: Pin82; TestPoint_Bridge_Pitch2.54mm_Drill1.3mm
J87: Pin84; TestPoint_Bridge_Pitch2.54mm_Drill1.3mm
J88: Pin86; TestPoint_Bridge_Pitch2.54mm_Drill1.3mm
J89: Pin88; TestPoint_Bridge_Pitch2.54mm_Drill1.3mm
J90: GND; TestPoint_Bridge_Pitch2.54mm_Drill1.3mm
LOGO1: Logo_Open_Hardware_Small; OSHW-Logo2_7.3x6mm_SilkScreen

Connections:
unnamed: J1.1, J2.1
unnamed: J1.2, J46.1
unnamed: J1.3, J3.1
unnamed: J1.4, J47.1
unnamed: J1.5, J4.1
unnamed: J1.6, J48.1
unnamed: J1.7, J5.1
unnamed: J1.8, J49.1
unnamed: J1.9, J6.1
unnamed: J1.10, J50.1
unnamed: J1.11, J7.1
unnamed: J1.12, J51.1
unnamed: J1.13, J8.1
unnamed: J1.14, J52.1
unnamed: J1.15, J9.1
unnamed: J1.16, J53.1
unnamed: J1.17, J10.1
unnamed: J1.18, J54.1
unnamed: J1.19, J11.1
unnamed: J1.20, J55.1
unnamed: J1.21, J12.1
unnamed: J1.22, J56.1
unnamed: J1.23, J13.1
unnamed: J1.24, J57.1
unnamed: J1.25, J14.1
unnamed: J1.26, J58.1
unnamed: J1.27, J15.1
unnamed: J1.28, J59.1
unnamed: J1.29, J16.1
unnamed: J1.30, J60.1
unnamed: J1.31, J17.1
unnamed: J1.32, J61.1
unnamed: J1.33, J18.1
unnamed: J1.34, J62.1
unnamed: J1.35, J19.1
unnamed: J1.36, J63.1
unnamed: J1.37, J20.1
unnamed: J1.38, J64.1
unnamed: J1.39, J21.1
unnamed: J1.40, J65.1
unnamed: J1.41, J22.1
unnamed: J1.42, J66.1
unnamed: J1.43, J23.1
unnamed: J1.44, J67.1
unnamed: J1.45, J24.1
unnamed: J1.46, J68.1
unnamed: J1.47, J25.1
unnamed: J1.48, J69.1
unnamed: J1.49, J26.1
unnamed: J1.50, J70.1
unnamed: J1.51, J27.1
unnamed: J1.52, J71.1
unnamed: J1.53, J28.1
unnamed: J1.54, J72.1
unnamed: J1.55, J29.1
unnamed: J1.56, J73.1
unnamed: J1.57, J30.1
unnamed: J1.58, J74.1
unnamed: J1.59, J31.1
unnamed: J1.60, J75.1
unnamed: J1.61, J32.1
unnamed: J1.62, J76.1
unnamed: J1.63, J33.1
unnamed: J1.64, J77.1
unnamed: J1.65, J34.1
unnamed: J1.66, J78.1
unnamed: J1.67, J35.1
unnamed: J1.68, J79.1
unnamed: J1.69, J36.1
unnamed: J1.70, J80.1
unnamed: J1.71, J37.1
unnamed: J1.72, J81.1
unnamed: J1.73, J38.1
unnamed: J1.74, J82.1
unnamed: J1.75, J39.1
unnamed: J1.76, J83.1
unnamed: J1.77, J40.1
unnamed: J1.78, J84.1
unnamed: J1.79, J41.1
unnamed: J1.80, J85.1
unnamed: J1.81, J42.1
unnamed: J1.82, J86.1
unnamed: J1.83, J43.1
unnamed: J1.84, J87.1
unnamed: J1.85, J44.1
unnamed: J1.86, J88.1
unnamed: J1.87, J45.1
unnamed: J1.88, J89.1

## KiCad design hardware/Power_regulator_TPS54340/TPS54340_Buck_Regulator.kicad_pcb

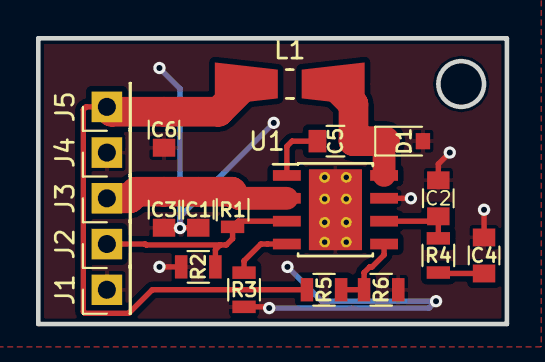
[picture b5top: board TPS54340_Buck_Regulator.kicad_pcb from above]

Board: 2 copper layers, 26.0 x 15.9 mm, 20 parts (0 on the bottom side), 10 nets.

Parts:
C1, C3: 2.2uF; C_0805
C2: 47pF; C_0805
C4: 5600pF; C_0805
C5: 0.1uF; C_0805
C6: 100uF; C_0805
D1: B560C; D_0805
J1, J2, J3, J4, J5: Conn_01x01; Pin_Header_Straight_1x01_Pitch2.54mm
L1: 5.6uH; Resistor_SMDuniversal_0805to1206_HandSoldering
R1: 365k; R_0805
R2: 86k6; R_0805
R3: 162k; R_0805
R4: 11k5; R_0805
R5: 31.6; R_0805
R6: 10.2; R_0805
U1: TPS54340; TI_SO-PowerPAD-8_ThermalVias

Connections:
/BOOT: C5.2, U1.1
/COMP: C2.1, R4.1, U1.6
/EN: J2.1, R1.1, R2.1, U1.3
/FB: R5.2, R6.1, U1.5
/RT/CLK: R3.1, U1.4
/SW: C5.1, D1.1, L1.1, U1.8
/VIN: C1.2, C3.2, J3.1, R1.2, U1.2
/VOUT: C6.1, J5.1, L1.2, R5.1
GND: C1.1, C2.2, C3.1, C4.2, C6.2, D1.2, J1.1, J4.1, R2.2, R3.2, R6.2, U1.7, U1.9
unnamed: C4.1, R4.2

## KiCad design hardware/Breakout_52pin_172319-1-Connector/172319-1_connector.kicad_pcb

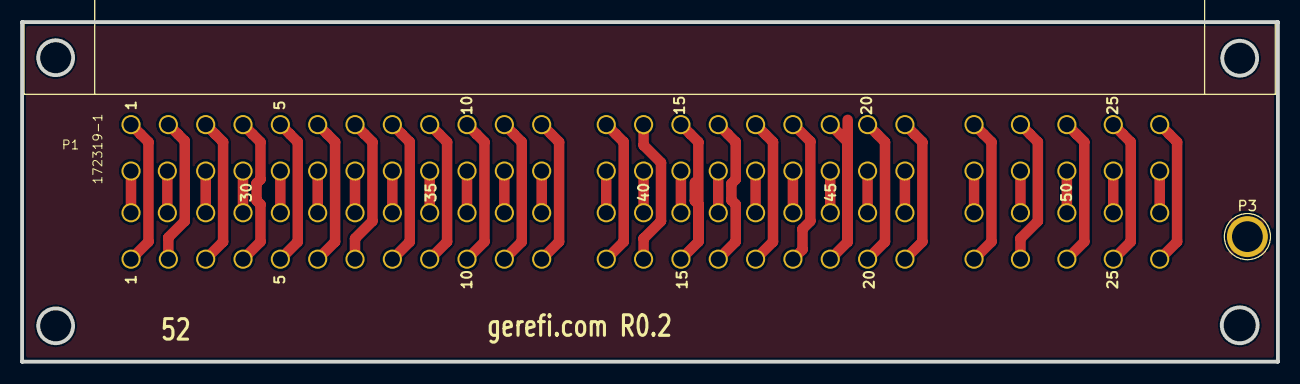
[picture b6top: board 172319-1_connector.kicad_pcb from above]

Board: 2 copper layers, 124.5 x 33.7 mm, 3 parts (1 on the bottom side), 52 nets.

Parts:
P1, P2: 172319-1; 172319-1_connector
P3: CONN_01X01; 1pin

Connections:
unnamed: P1.1, P2.1
unnamed: P1.2, P2.2
unnamed: P1.3, P2.3
unnamed: P1.4, P2.4
unnamed: P1.5, P2.5
unnamed: P1.6, P2.6
unnamed: P1.7, P2.7
unnamed: P1.8, P2.8
unnamed: P1.9, P2.9
unnamed: P1.10, P2.10
unnamed: P1.11, P2.11
unnamed: P1.12, P2.12
unnamed: P1.13, P2.13
unnamed: P1.14, P2.14
unnamed: P1.15, P2.15
unnamed: P1.16, P2.16
unnamed: P1.17, P2.17
unnamed: P1.18, P2.18
unnamed: P1.19, P2.19
unnamed: P1.20, P2.20
unnamed: P1.21, P2.21
unnamed: P1.22, P2.22
unnamed: P1.23, P2.23
unnamed: P1.24, P2.24
unnamed: P1.25, P2.25
unnamed: P1.26, P2.26
unnamed: P1.27, P2.27
unnamed: P1.28, P2.28
unnamed: P1.29, P2.29
unnamed: P1.30, P2.30
unnamed: P1.31, P2.31
unnamed: P1.32, P2.32
unnamed: P1.33, P2.33
unnamed: P1.34, P2.34
unnamed: P1.35, P2.35
unnamed: P1.36, P2.36
unnamed: P1.37, P2.37
unnamed: P1.38, P2.38
unnamed: P1.39, P2.39
unnamed: P1.40, P2.40
unnamed: P1.41, P2.41
unnamed: P1.42, P2.42
unnamed: P1.43, P2.43
unnamed: P1.44, P2.44
unnamed: P1.45, P2.45
unnamed: P1.46, P2.46
unnamed: P1.47, P2.47
unnamed: P1.48, P2.48
unnamed: P1.49, P2.49
unnamed: P1.50, P2.50
unnamed: P1.51, P2.51
unnamed: P1.52, P2.52
